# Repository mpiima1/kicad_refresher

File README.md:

# demo project

A small KiCad learning project. I work mostly in Altium, so I built this board
end-to-end in KiCad to pick up the basics of the toolchain: schematic capture,
symbol/footprint libraries, net classes, placement and routing, and
manufacturing output. It is a tutorial reproduction, not original design work.

## Tutorial

Followed along with Phil's Lab KiCad 9 hardware design tutorial (TI MSPM0):

- Part 1 — Schematic: <https://www.youtube.com/watch?v=O-zNn5k5Bn4> (Phil's Lab #165)
- Part 2 — PCB: <https://www.youtube.com/watch?v=igQWdVGZGpI> (Phil's Lab #166)

## Hardware overview

2-layer dev board built around:

| Block | Part |
| --- | --- |
| MCU | TI MSPM0G3507 (LQFP-64) |
| USB | USB-C receptacle + USBLC6-2SC6 ESD protection |
| USB-UART bridge | WCH CH340E |
| Sensor | ST LIS2DH accelerometer (I2C) |
| Power | SPX3819M5-L-3-3 3.3 V LDO from VBUS |
| Debug | SWD via Tag-Connect TC2030 footprint |
| Misc | Crystal, fiducials, mounting holes |

Custom net classes are used for `3V3`, `GND`, `I2C`, `SW`, `UART`, `USB`,
`VBUS`, and `XTAL`.

## PCB

The board is a compact 2-layer layout with routing done against the custom net
classes, and a Tag-Connect footprint for SWD debug:

3D render of the populated top side:

## Repo layout

```
demo project.kicad_pro     project file
demo project.kicad_sch     schematic
demo project.kicad_pcb     layout
mspmo.kicad_sym            project-local symbol library (MSPM0, CH340E, ...)
sym-lib-table              ties the local library to the project
screenshots/               images used in this README
demo project-backups/      KiCad automatic backups
```

Open `demo project.kicad_pro` in KiCad 9 so the project-local symbol library
resolves correctly. The tutorial is written for KiCad 9 and I started it there,
but I later updated to KiCad 10 and everything carried over without issues.

## Manufacturing outputs

Fabrication files (Gerbers, drill, BOM, position files) live in `manufacturing/`
locally but are intentionally **gitignored**, so they are not in this repo — it
contains design sources only. If you're new to KiCad, the two tutorial parts
above walk through generating these outputs, and you can also regenerate them
yourself from `demo project.kicad_pcb` via *File → Fabrication Outputs*.

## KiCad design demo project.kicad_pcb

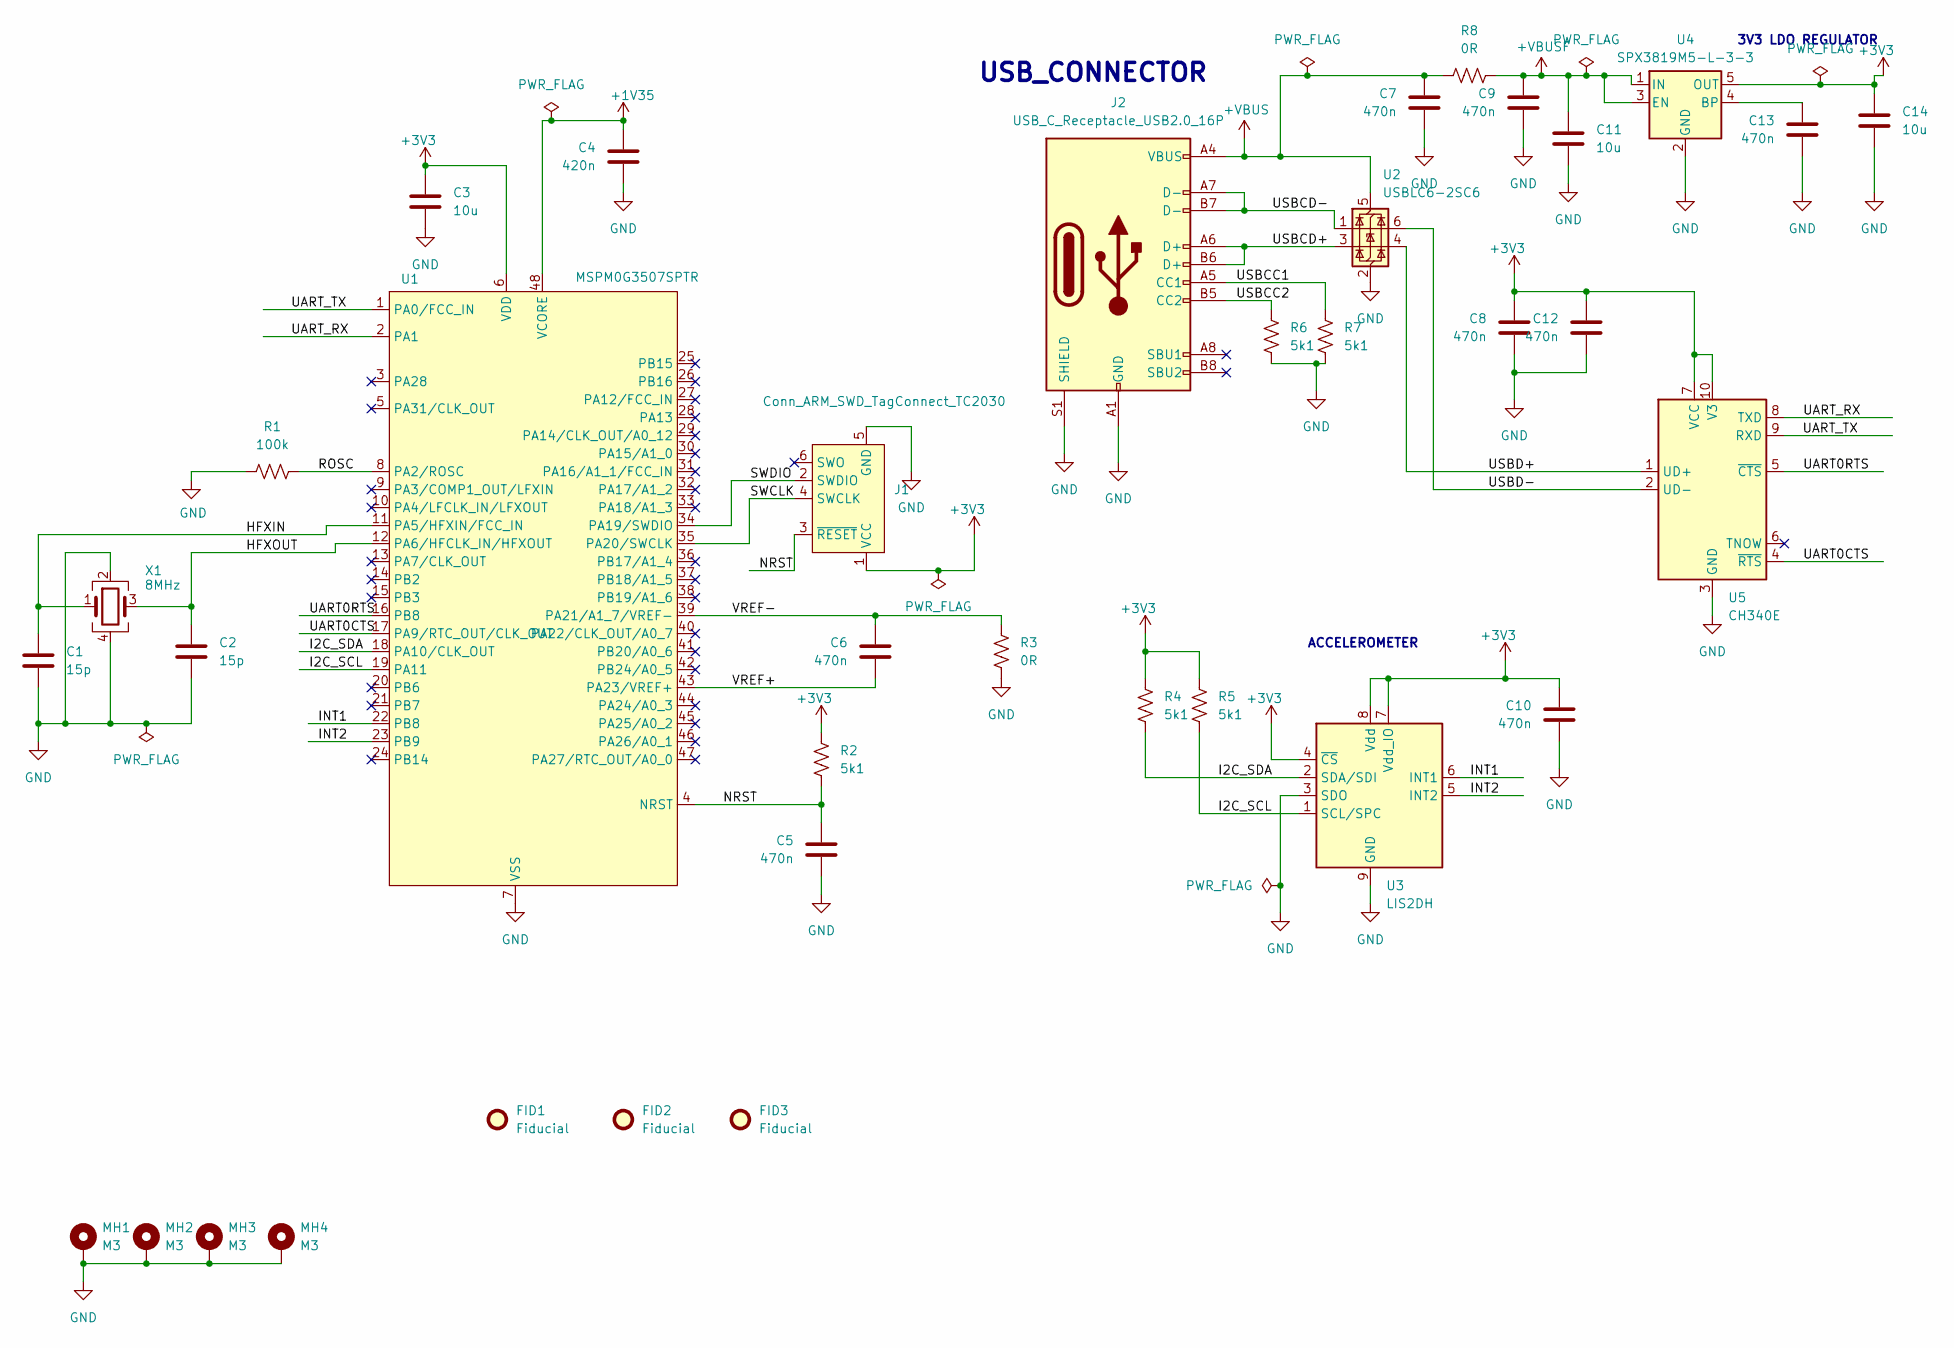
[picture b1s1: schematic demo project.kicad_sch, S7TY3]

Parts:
C1, C2: 15p; C_0805_2012Metric; Manufacturer Part Number CL21A106KOQNNNE; LCSC C1713
C3, C11, C14: 10u; C_0805_2012Metric; Manufacturer Part Number CL21A106KOQNNNE; LCSC C1713
C4: 420n; C_0603_1608Metric; Manufacturer Part Number TMK107B7474KA-TR; LCSC C386080
C5, C6, C7, C8, C9, C10, C12, C13: 470n; C_0603_1608Metric; Manufacturer Part Number TMK107B7474KA-TR; LCSC C386080
FID1, FID2, FID3: Fiducial; Fiducial_1mm_Mask2mm
J1: Conn_ARM_SWD_TagConnect_TC2030; Tag-Connect_TC2030-IDC-FP_2x03_P1.27mm_Vertical
J2: USB_C_Receptacle_USB2.0_16P; USB_C_Receptacle_GCT_USB4105-xx-A_16P_TopMnt_Horizontal
MH1, MH2, MH3, MH4: M3; MountingHole_3.2mm_M3_Pad_Via
R1: 100k; R_0603_1608Metric; Manufacturer Part Number CRT0603-BY-1003ELF; LCSC C4332041
R2, R4, R5, R6, R7: 5k1; R_0603_1608Metric; Manufacturer Part Number RC0603FR-075K1L; LCSC C105580
R3, R8: 0R; R_0603_1608Metric; Manufacturer Part Number RMCF0603ZT0R00; LCSC C2441282
U1: MSPM0G3507SPTR; LQFP-48_7x7mm_P0.5mm; Manufacturer Part Number MSPM0G3507SPTR; LCSC C22362630
U2: USBLC6-2SC6; SOT-23-6
U3: LIS2DH; LGA-14_2x2mm_P0.35mm_LayoutBorder3x4y
U4: SPX3819M5-L-3-3; SOT-23-5
U5: CH340E; MSOP-10_3x3mm_P0.5mm
X1: 8MHz; Crystal_SMD_3225-4Pin_3.2x2.5mm

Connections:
+1V35: C4.1, U1.48 (VCORE)
+3V3: C3.1, C8.1, C10.1, C12.1, C14.1, J1.1 (VCC), R2.1, R4.1, R5.1, U1.6 (VDD), U3.4 (~CS), U3.7 (Vdd_IO), U3.8 (Vdd), U4.5 (OUT), U5.7 (VCC), U5.10 (V3)
+VBUS: C7.1, J2.A4 (VBUS), J2.A9 (VBUS), J2.B4 (VBUS), J2.B9 (VBUS), R8.1, U2.5 (VBUS)
+VBUSF: C9.1, C11.1, R8.2, U4.1 (IN), U4.3 (EN)
/HFXIN: C1.1, U1.11 (PA5/HFXIN/FCC_IN), X1.1
/HFXOUT: C2.1, U1.12 (PA6/HFCLK_IN/HFXOUT), X1.3
/I2C_SCL: R5.2, U1.19 (PA11), U3.1 (SCL/SPC)
/I2C_SDA: R4.2, U1.18 (PA10/CLK_OUT), U3.2 (SDA/SDI)
/INT1: U1.22 (PB8), U3.6 (INT1)
/INT2: U1.23 (PB9), U3.5 (INT2)
/NRST: C5.1, J1.3 (~RESET), R2.2, U1.4 (NRST)
/ROSC: R1.2, U1.8 (PA2/ROSC)
/SWCLK: J1.4 (SWCLK), U1.35 (PA20/SWCLK)
/SWDIO: J1.2 (SWDIO), U1.34 (PA19/SWDIO)
/UART0CTS: U1.17 (PA9/RTC_OUT/CLK_OUT), U5.4 (~RTS)
/UART0RTS: U1.16 (PB8), U5.5 (~CTS)
/UART_RX: U1.2 (PA1), U5.8 (TXD)
/UART_TX: U1.1 (PA0/FCC_IN), U5.9 (RXD)
/USBCC1: J2.A5 (CC1), R7.1
/USBCC2: J2.B5 (CC2), R6.1
/USBCD+: J2.A6 (D+), J2.B6 (D+), U2.3 (I/O2)
/USBCD-: J2.A7 (D-), J2.B7 (D-), U2.1 (I/O1)
/USBD+: U2.4 (I/O2), U5.1 (UD+)
/USBD-: U2.6 (I/O1), U5.2 (UD-)
/VREF+: C6.2, U1.43 (PA23/VREF+)
/VREF-: C6.1, R3.1, U1.39 (PA21/A1_7/VREF-)
GND: C1.2, C2.2, C3.2, C4.2, C5.2, C7.2, C8.2, C9.2, C10.2, C11.2, C12.2, C13.2, C14.2, J1.5 (GND), J2.A1 (GND), J2.A12 (GND), J2.B1 (GND), J2.B12 (GND), J2.S1 (SHIELD), MH1.1 (1_1), MH2.1 (1_1), MH3.1 (1_1), MH4.1 (1_1), R1.1, R3.2, R6.2, R7.2, U1.7 (VSS), U2.2 (GND), U3.3 (SDO), U3.9 (GND), U3.10 (GND), U3.11 (GND), U3.12 (GND), U3.13 (GND), U3.14 (GND), U4.2 (GND), U5.3 (GND), X1.2, X1.4
unnamed: C13.1, U4.4 (BP)

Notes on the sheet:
ACCELEROMETER
USB_CONNECTOR
3V3 LDO REGULATOR

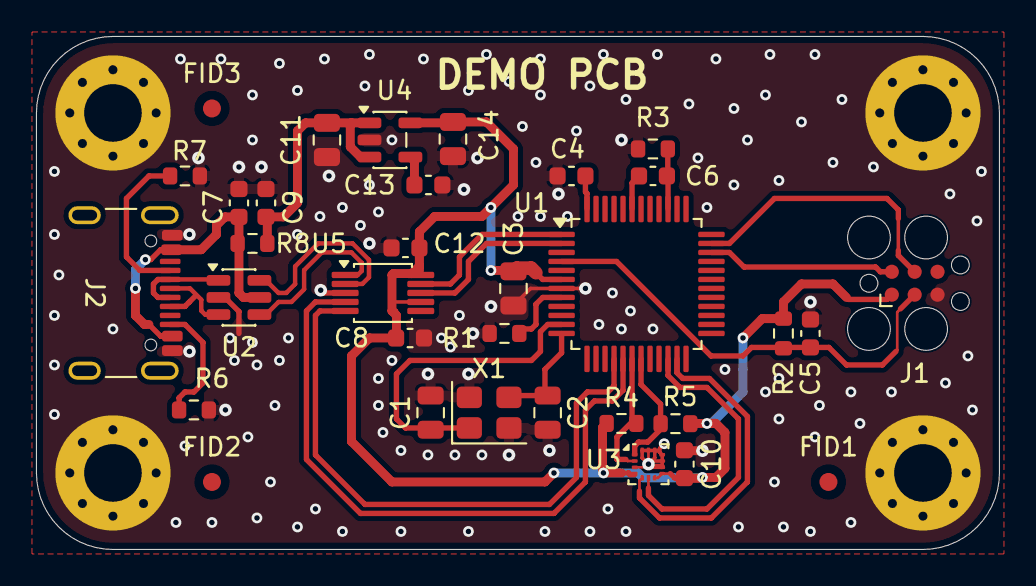
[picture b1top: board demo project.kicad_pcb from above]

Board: 2 copper layers, 53.5 x 28.5 mm, 37 parts (0 on the bottom side), 28 nets.
